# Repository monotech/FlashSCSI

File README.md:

Intended for classic Macs starting with the Macintosh Plus, this is a Super-miniature clone of the SCSI2SD v4.2b by Michael McMaster.

Original SCSI2SD source files here: http://www.codesrc.com/gitweb/index.cgi?p=SCSI2SD.git;a=tree

If the semiconductor shortage hasn't caused them to dry up, I should have assembled stock for sale at http://monotech.fwscart.com

Mechanical parts required for assembly of the enclosure panels:
2 x screws: 2-56 UNC, 5/32" long
2 x nuts: 2-56 UNC
4 x M-F hex spacers: 3/16" body length, 5/32" screw length, 2-56 UNC thread. Example part: Fascomp FC4500-256-A

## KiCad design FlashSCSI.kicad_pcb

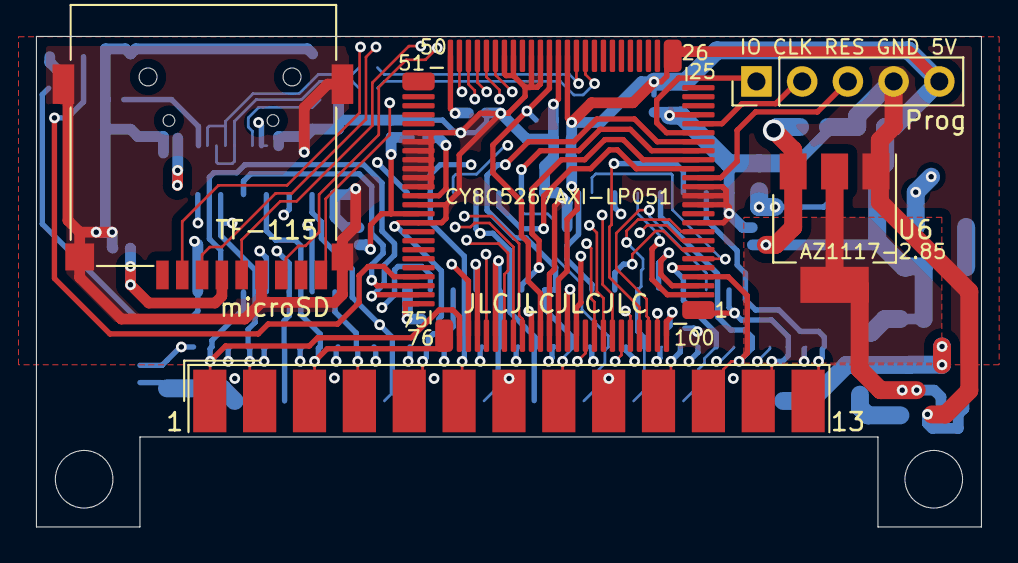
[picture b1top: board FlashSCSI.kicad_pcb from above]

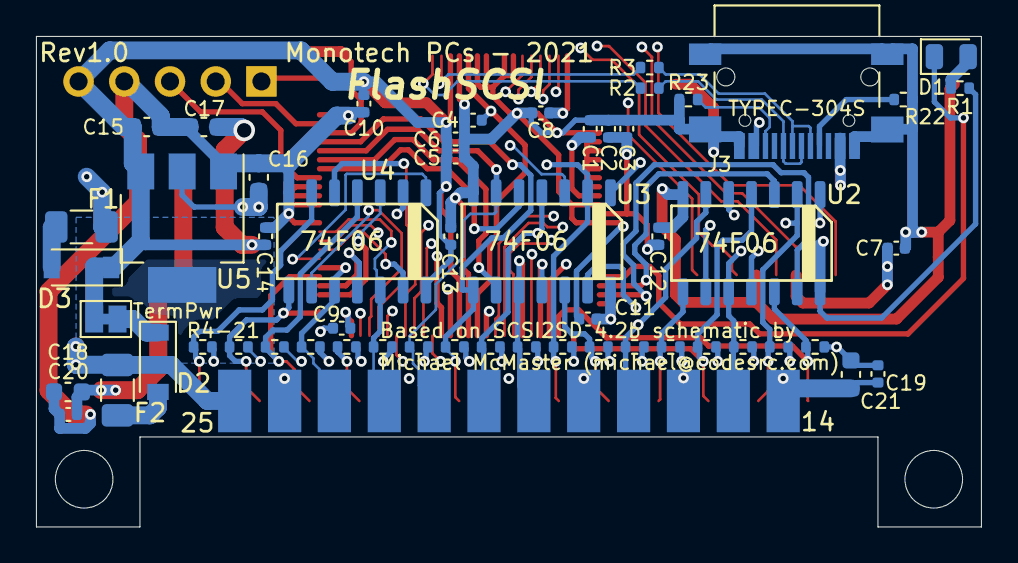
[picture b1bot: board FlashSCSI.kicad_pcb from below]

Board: 4 copper layers, 52.5 x 27.2 mm, 60 parts (55 on the bottom side), 63 nets.

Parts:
C1, C2, C4, C5: 1uF; C_0402_1005Metric
C3, C6, C7, C8, C9, C10, C11, C12, C13, C14, C19, C20: 100nF; C_0402_1005Metric
C15, C16, C17, C18, C21: 10uF; C_0603_1608Metric
D1: Activity; LED_0805_2012Metric
D2, D3: B5819W; D_SOD-123
F1, F2: 1A; Fuse_1206_3216Metric
J1: Prog; PinHeader_1x05_P2.54mm_Vertical
J2: microSD; microSD_HC_XunPu_TF-115
J3: USB; USB_C_Receptacle_XunPu_TYPEC-304S
J4: SCSI; DSUB-25_Male_EdgeMount_P2.77mm
JP1: TermPwr; SolderJumper-2_P1.3mm_Bridged_Pad1.0x1.5mm
R1: 2.2k; R_0402_1005Metric
R2, R3: 22; R_0402_1005Metric
R4, R5, R6, R7, R8, R9, R10, R11, R12, R13, R14, R15, R16, R17, R18, R19, R20, R21: 110; R_0402_1005Metric
R22, R23: 5.6k; R_0402_1005Metric
U1: CY8C5267AXI-LP051; LQFP-100_14x14mm_P0.5mm
U2, U3, U4: 74F06; SOIC-14_3.9x8.7mm_P1.27mm
U5: AZ1117-3.3; SOT-223-3_TabPin2
U6: AZ1117-2.85; SOT-223-3_TabPin2

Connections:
+3V3: C7.1, C8.1, C16.1, J2.4, U1.50, U5.2
+5V: C2.1, C3.1, C5.1, C6.1, C9.1, C10.1, C11.1, C12.1, C13.1, C14.1, C15.1, C17.1, D3.1, J1.5, JP1.2, R1.1, U1.26, U1.37, U1.65, U1.75, U1.88, U1.100, U2.14, U3.14, U4.14, U5.3, U6.3
/ACK: U1.89, U3.13
/ATN: U1.93, U2.5
/BSY: U1.90, U3.1
/CD: U1.78, U2.11
/C_USBD+: J3.A6, J3.B6, R2.2
/C_USBD-: J3.A7, J3.B7, R3.2
/DB0: U1.17, U3.9
/DB1: U1.16, U3.5
/DB2: U1.7, U4.13
/DB3: U1.6, U4.1
/DB4: U1.3, U4.11
/DB5: U1.2, U4.3
/DB6: U1.98, U4.9
/DB7: U1.97, U4.5
/DBP: U1.94, U3.3
/IO: U1.73, U2.3
/MSG: U1.82, U2.1
/REQ: U1.74, U2.13
/RST: U1.83, U2.9
/SD_MISO: J2.7, U1.45
/SD_MOSI: J2.3, U1.47
/SD_SCK: J2.5, U1.46
/SEL: U1.79, U3.11
/SWDCLK: J1.2, U1.21
/SWDIO: J1.1, U1.20
/Term_Pwr: F2.2, J4.25
/USBD+: R2.1, U1.35
/USBD-: R3.1, U1.36
/~ACK: J4.5, R19.1, U1.91, U3.12
/~ATN: J4.17, R21.1, U1.95, U2.6
/~BSY: J4.6, R20.1, U1.92, U3.2
/~CD: J4.15, R15.1, U1.80, U2.10
/~DB0: J4.8, R12.1, U1.19, U3.8
/~DB1: J4.21, R11.1, U1.18, U3.6
/~DB2: J4.22, R10.1, U1.9, U4.12
/~DB3: J4.10, R9.1, U1.8, U4.2
/~DB4: J4.23, R8.1, U1.5, U4.10
/~DB5: J4.11, R7.1, U1.4, U4.4
/~DB6: J4.12, R6.1, U1.1, U4.8
/~DB7: J4.13, R5.1, U1.99, U4.6
/~DBP: J4.20, R4.1, U1.96, U3.4
/~IO: J4.3, R13.1, U1.76, U2.4
/~MSG: J4.2, R17.1, U1.84, U2.2
/~REQ: J4.1, R14.1, U1.77, U2.12
/~RST: J4.4, R18.1, U1.85, U2.8
/~SD_CD: J2.9, U1.49
/~SD_CS: J2.2, U1.48
/~SEL: J4.19, R16.1, U1.81, U3.10
/~XRES: J1.3, U1.15
GND: C1.2, C2.2, C3.2, C4.2, C5.2, C6.2, C7.2, C8.2, C9.2, C10.2, C11.2, C12.2, C13.2, C14.2, C15.2, C16.2, C17.2, C18.2, C19.2, C20.2, C21.2, J1.4, J2.6, J2.10, J3.A1, J3.A12, J3.B1, J3.B12, J3.S1, J4.7, J4.9, J4.14, J4.16, J4.18, J4.24, R22.1, R23.1, U1.10, U1.12, U1.13, U1.14, U1.22, U1.38, U1.40, U1.41, U1.43, U1.44, U1.56, U1.57, U1.58, U1.59, U1.60, U1.61, U1.62, U1.64, U1.66, U1.87, U2.7, U3.7, U4.7, U5.1, U6.1
unnamed: C1.1, U1.63
unnamed: C4.1, U1.39, U1.86
unnamed: C18.1, C19.1, C20.1, C21.1, R4.2, R5.2, R6.2, R7.2, R8.2, R9.2, R10.2, R11.2, R12.2, R13.2, R14.2, R15.2, R16.2, R17.2, R18.2, R19.2, R20.2, R21.2, U6.2
unnamed: D1.1, U1.72
unnamed: D1.2, R1.2
unnamed: D2.1, JP1.1
unnamed: D2.2, F2.1
unnamed: D3.2, F1.1
unnamed: F1.2, J3.A4, J3.A9, J3.B4, J3.B9
unnamed: J3.A5, R22.2
unnamed: J3.B5, R23.2
